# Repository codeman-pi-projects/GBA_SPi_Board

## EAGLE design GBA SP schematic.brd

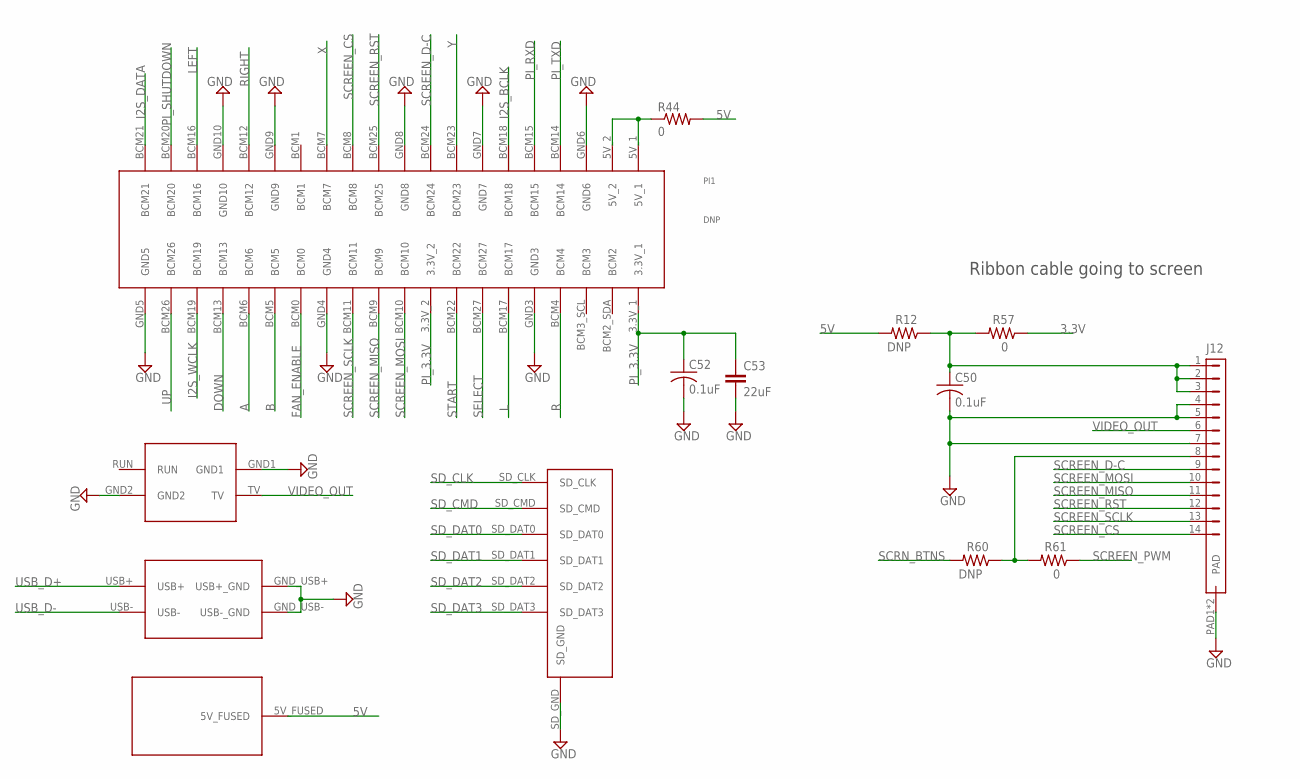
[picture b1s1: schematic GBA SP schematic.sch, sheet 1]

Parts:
C50, C52: 0.1uF; 0402_REAL; MPN CC0603ZRY5V9BB104; DIGIKEY 311-1343-1-ND
C53: 22uF; C0805; MPN LMK212BBJ226MG-T; DIGIKEY 587-5464-1-ND
J12: FPC_14; MPN 5051101492; DIGIKEY WM12370CT-ND
PI1: DNP; PI-ZERO
R12: DNP; R0603
R44: 0; R0805
R57: 0; R0603
R60: DNP; 0402_REAL
R61: 0; 0402_REAL

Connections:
3.3V: R57.1; also elsewhere on the board
5V: PI1.5V_FUSED, R12.2, R44.2; also elsewhere on the board
A: PI1.BCM6; also elsewhere on the board
B: PI1.BCM5; also elsewhere on the board
DOWN: PI1.BCM13; also elsewhere on the board
FAN_ENABLE: PI1.BCM0; also elsewhere on the board
GND: C50.2, C52.2, C53.2, J12.4, J12.5, J12.7, J12.PAD1 (PAD), J12.PAD2 (PAD), PI1.GND1, PI1.GND2, PI1.GND3, PI1.GND4, PI1.GND5, PI1.GND6, PI1.GND7, PI1.GND8, PI1.GND9, PI1.GND10, PI1.GND_USB+ (USB+_GND), PI1.GND_USB- (USB-_GND), PI1.SD_GND; also elsewhere on the board
I2S_BCLK: PI1.BCM18; also elsewhere on the board
I2S_DATA: PI1.BCM21; also elsewhere on the board
I2S_WCLK: PI1.BCM19; also elsewhere on the board
L: PI1.BCM17; also elsewhere on the board
LEFT: PI1.BCM16; also elsewhere on the board
unnamed: PI1.5V_1, PI1.5V_2, R44.1
unnamed: J12.8, R60.1, R61.2
unnamed: C50.1, J12.1, J12.2, J12.3, R12.1, R57.2
PI_3.3V: C52.1, C53.1, PI1.3.3V_1, PI1.3.3V_2; also elsewhere on the board
PI_RXD: PI1.BCM15; also elsewhere on the board
PI_SHUTDOWN: PI1.BCM20; also elsewhere on the board
PI_TXD: PI1.BCM14; also elsewhere on the board
R: PI1.BCM4; also elsewhere on the board
RIGHT: PI1.BCM12; also elsewhere on the board
SCREEN_CS: J12.14, PI1.BCM8
SCREEN_D-C: J12.9, PI1.BCM24
SCREEN_MISO: J12.11, PI1.BCM9
SCREEN_MOSI: J12.10, PI1.BCM10
SCREEN_PWM: R61.1; also elsewhere on the board
SCREEN_RST: J12.12, PI1.BCM25
SCREEN_SCLK: J12.13, PI1.BCM11
SCRN_BTNS: R60.2; also elsewhere on the board
SD_CLK: PI1.SD_CLK
SD_CMD: PI1.SD_CMD
SD_DAT0: PI1.SD_DAT0
SD_DAT1: PI1.SD_DAT1
SD_DAT2: PI1.SD_DAT2
SD_DAT3: PI1.SD_DAT3
SELECT: PI1.BCM27; also elsewhere on the board
START: PI1.BCM22; also elsewhere on the board
UP: PI1.BCM26; also elsewhere on the board
USB_D+: PI1.USB+; also elsewhere on the board
USB_D-: PI1.USB-; also elsewhere on the board
VIDEO_OUT: J12.6, PI1.TV
X: PI1.BCM7; also elsewhere on the board
Y: PI1.BCM23; also elsewhere on the board

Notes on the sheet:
Ribbon cable going to screen

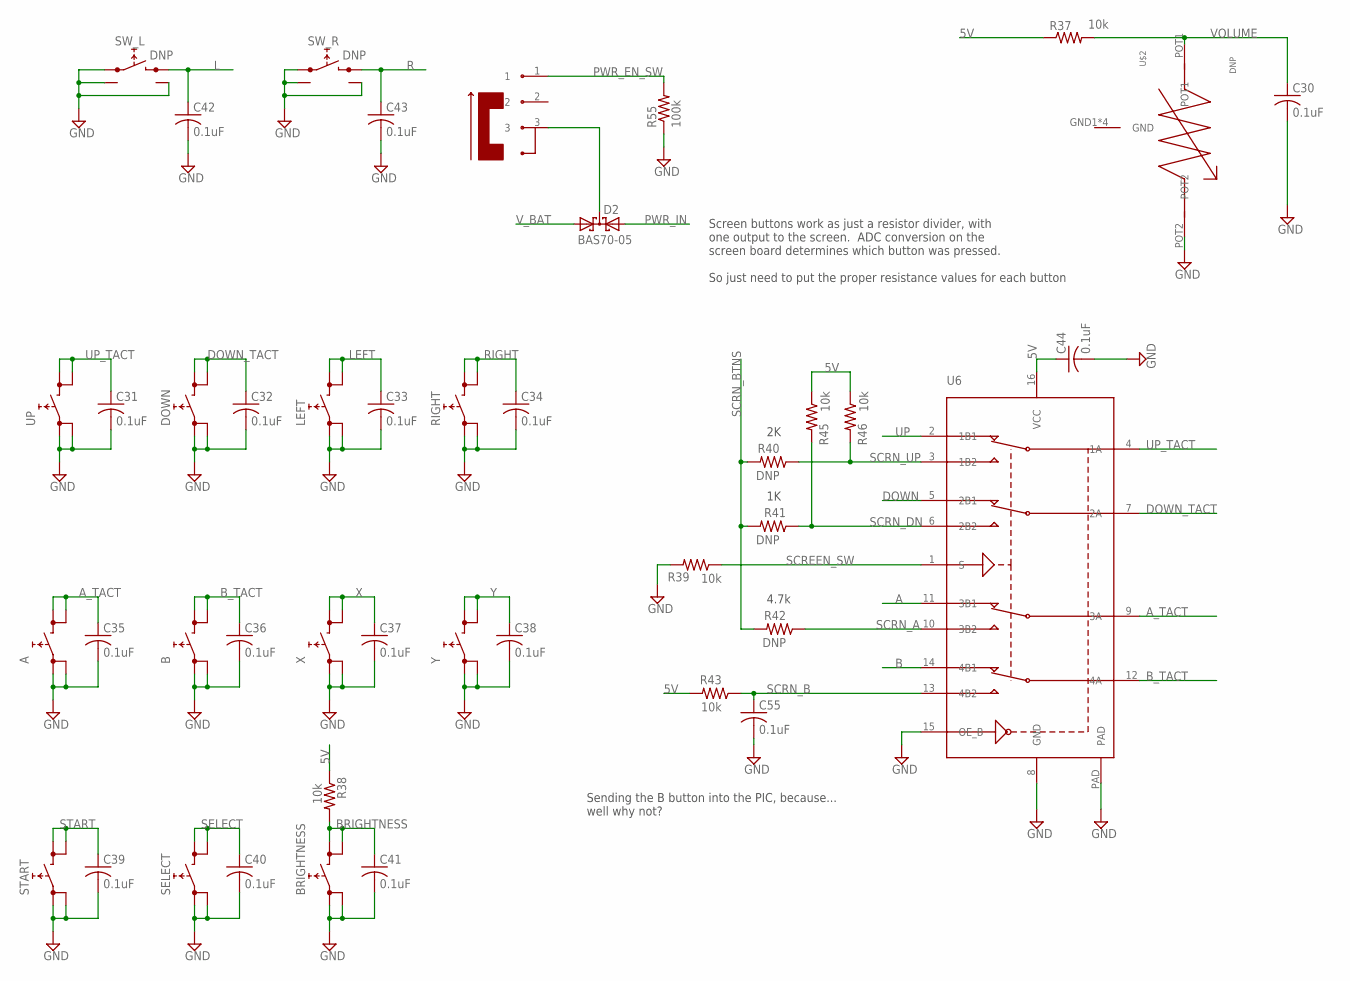
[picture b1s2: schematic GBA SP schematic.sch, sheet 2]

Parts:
A: TACTILEGBA_SP; GBA_SP_TACT; MPN SKRRAAE010; MOUSER 688-SKRRAA
B: TACTILEGBA_SP; GBA_SP_TACT; MPN SKRRAAE010; MOUSER 688-SKRRAA
BRIGHTNESS: TACTILE; TL3315; MPN TL3315NF160Q; DIGIKEY EG4621CT-ND
C30, C31, C32, C33, C34, C35, C36, C37, C38, C39, C40, C41, C42, C43, C44, C55: 0.1uF; 0402_REAL; MPN CC0603ZRY5V9BB104; DIGIKEY 311-1343-1-ND
D2: BAS70-05; SOT23; MPN BAS70-05-E3-08; DIGIKEY BAS70-05-E3-08CT-ND
DOWN: TACTILEGBA_SP; GBA_SP_TACT; MPN SKRRAAE010; MOUSER 688-SKRRAA
LEFT: TACTILEGBA_SP; GBA_SP_TACT; MPN SKRRAAE010; MOUSER 688-SKRRAA
R37, R38, R39, R43, R45, R46: 10k; 0402_REAL
R40: DNP; 0402_REAL; MPN ERJ-2RKF2001X; DIGIKEY P2.00KLCT-ND
R41, R42: DNP; 0402_REAL
R55: 100k; 0402_REAL; MPN RC0402FR-07100KL; DIGIKEY 311-100KLRCT-ND
RIGHT: TACTILEGBA_SP; GBA_SP_TACT; MPN SKRRAAE010; MOUSER 688-SKRRAA
SELECT: TACTILE; TL3315; MPN TL3315NF160Q; DIGIKEY EG4621CT-ND
START: TACTILE; TL3315; MPN TL3315NF160Q; DIGIKEY EG4621CT-ND
SW_L: DNP; GBA-SHOULDER-SW
SW_R: DNP; GBA-SHOULDER-SW
U6: SN74CBT3257C; VQFN16; MPN SN74CBT3257CRGYR; DIGIKEY 296-19212-1-ND
U$1: CSS-1210; MPN CSS-1210TB
U$2: DNP; GBA-POT
UP: TACTILEGBA_SP; GBA_SP_TACT; MPN SKRRAAE010; MOUSER 688-SKRRAA
X: TACTILEGBA_SP; GBA_SP_TACT; MPN SKRRAAE010; MOUSER 688-SKRRAA
Y: TACTILEGBA_SP; GBA_SP_TACT; MPN SKRRAAE010; MOUSER 688-SKRRAA

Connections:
5V: C44.1, R37.1, R38.1, R43.2, R45.1, R46.1, U6.16 (VCC); also elsewhere on the board
A: U6.11 (3B1); also elsewhere on the board
A_TACT: A.2 (3), A.4, C35.1, U6.9 (3A)
B: U6.14 (4B1); also elsewhere on the board
BRIGHTNESS: BRIGHTNESS.3, BRIGHTNESS.4, C41.1, R38.2; also elsewhere on the board
B_TACT: B.2 (3), B.4, C36.1, U6.12 (4A)
DOWN: U6.5 (2B1); also elsewhere on the board
DOWN_TACT: C32.1, DOWN.2 (3), DOWN.4, U6.7 (2A)
GND: A.1, A.3 (2), B.1, B.3 (2), BRIGHTNESS.1, BRIGHTNESS.2, C30.2, C31.2, C32.2, C33.2, C34.2, C35.2, C36.2, C37.2, C38.2, C39.2, C40.2, C41.2, C42.2, C43.2, C44.2, C55.2, DOWN.1, DOWN.3 (2), LEFT.1, LEFT.3 (2), R39.2, R55.1, RIGHT.1, RIGHT.3 (2), SELECT.1, SELECT.2, START.1, START.2, SW_L.A, SW_L.GND1, SW_L.GND2, SW_R.A, SW_R.GND1, SW_R.GND2, U6.8 (GND), U6.15 (OE_B), U6.PAD, U$2.POT2, UP.1, UP.3 (2), X.1, X.3 (2), Y.1, Y.3 (2); also elsewhere on the board
L: C42.1, SW_L.B; also elsewhere on the board
LEFT: C33.1, LEFT.2 (3), LEFT.4; also elsewhere on the board
unnamed: D2.3 (C), U$1.3
PWR_EN_SW: R55.2, U$1.1; also elsewhere on the board
PWR_IN: D2.2 (A2); also elsewhere on the board
R: C43.1, SW_R.B; also elsewhere on the board
RIGHT: C34.1, RIGHT.2 (3), RIGHT.4; also elsewhere on the board
SCREEN_SW: R39.1, U6.1 (S); also elsewhere on the board
SCRN_A: R42.1, U6.10 (3B2)
SCRN_B: C55.1, R43.1, U6.13 (4B2); also elsewhere on the board
SCRN_BTNS: R40.2, R41.2, R42.2; also elsewhere on the board
SCRN_DN: R41.1, R45.2, U6.6 (2B2); also elsewhere on the board
SCRN_UP: R40.1, R46.2, U6.3 (1B2); also elsewhere on the board
SELECT: C40.1, SELECT.3, SELECT.4; also elsewhere on the board
START: C39.1, START.3, START.4; also elsewhere on the board
UP: U6.2 (1B1); also elsewhere on the board
UP_TACT: C31.1, U6.4 (1A), UP.2 (3), UP.4
VOLUME: C30.1, R37.2, U$2.POT1; also elsewhere on the board
V_BAT: D2.1 (A1); also elsewhere on the board
X: C37.1, X.2 (3), X.4; also elsewhere on the board
Y: C38.1, Y.2 (3), Y.4; also elsewhere on the board

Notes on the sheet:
Screen buttons work as just a resistor divider, with one output to the screen. ADC conversion on the screen board determines which button was pressed. So just need to put the proper resistance values for each button
Sending the B button into the PIC, because... well why not?
4.7k

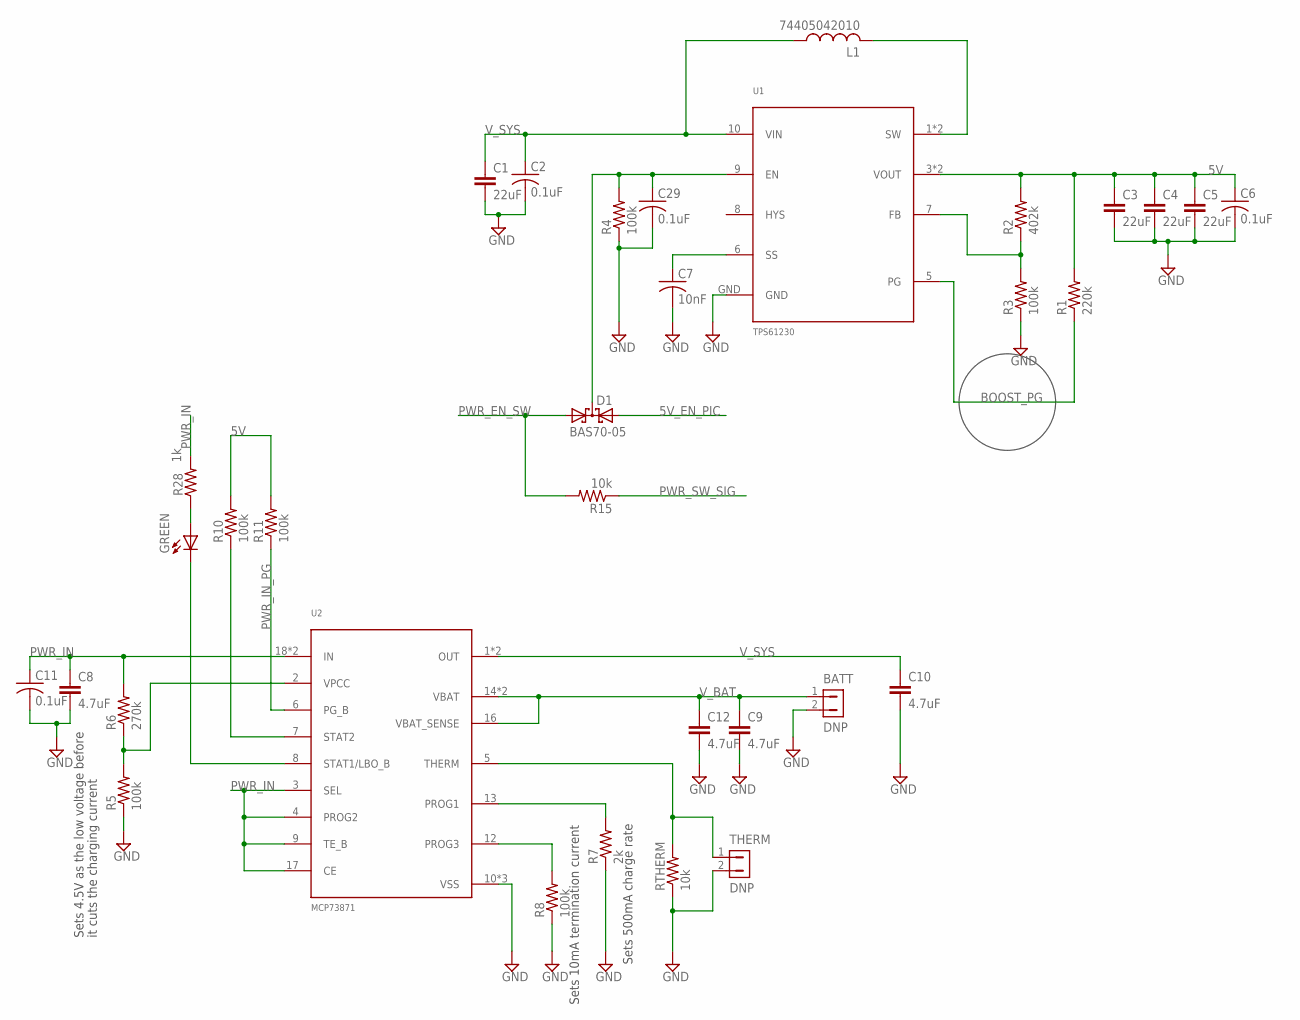
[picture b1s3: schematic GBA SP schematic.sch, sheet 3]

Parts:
BATT: DNP; HEADER-1X2
C1, C3, C4, C5: 22uF; C0805; MPN LMK212BBJ226MG-T; DIGIKEY 587-5464-1-ND
C2, C6, C11, C29: 0.1uF; 0402_REAL; MPN CC0603ZRY5V9BB104; DIGIKEY 311-1343-1-ND
C7: 10nF; 0402_REAL; MPN GRM155R71H103KA88D; DIGIKEY 490-4516-1-ND
C8, C9, C10, C12: 4.7uF; C0603; MPN CC0603KRX5R6BB475; DIGIKEY 311-1455-1-ND
D1: BAS70-05; SOT23; MPN BAS70-05-E3-08; DIGIKEY BAS70-05-E3-08CT-ND
GREEN: LEDCHIP-LED0603; CHIP-LED0603; MPN LTST-C191KGKT; DIGIKEY 160-1446-1-ND
L1: 74405042010; XFL4020-102MEB; MPN 74405042010
R1: 220k; R0603
R2: 402k; 0402_REAL; MPN RC0402FR-07402KL; DIGIKEY YAG3151CT-ND
R3, R4, R5, R8, R10, R11: 100k; 0402_REAL; MPN RC0402FR-07100KL; DIGIKEY 311-100KLRCT-ND
R6: 270k; R0603; MPN RC0402JR-07270KL; DIGIKEY 311-270KJRCT-ND
R7: 2k; 0402_REAL; MPN ERJ-2RKF2001X; DIGIKEY P2.00KLCT-ND
R15: 10k; 0402_REAL
R28: 1k; 0402_REAL
RTHERM: 10k; 0402_REAL
THERM: DNP; DF13-2_THIN
U1: TPS61230; VSON10; MPN TPS61230DRCR; DIGIKEY 296-37761-1-ND
U2: MCP73871; QFN20; MPN MCP73871-2AAI/ML; DIGIKEY MCP73871-2AAI/ML-ND

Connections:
5V: C3.1, C4.1, C5.1, C6.1, R1.2, R2.2, R10.2, R11.2, U1.3 (VOUT), U1.4 (VOUT); also elsewhere on the board
5V_EN_PIC: D1.2 (A2); also elsewhere on the board
BOOST_PG: R1.1, U1.5 (PG)
GND: BATT.2, C1.2, C2.2, C3.2, C4.2, C5.2, C6.2, C7.2, C8.2, C9.2, C10.2, C11.2, C12.2, C29.2, R3.1, R4.1, R5.1, R7.1, R8.1, RTHERM.1, THERM.2, U1.GND, U2.10 (VSS), U2.11 (VSS), U2.PAD (VSS); also elsewhere on the board
unnamed: C29.1, D1.3 (C), R4.2, U1.9 (EN)
unnamed: L1.2, U1.1 (SW), U1.2 (SW)
unnamed: R2.1, R3.2, U1.7 (FB)
unnamed: R7.2, U2.13 (PROG1)
unnamed: R5.2, R6.1, U2.2 (VPCC)
unnamed: C7.1, U1.6 (SS)
unnamed: R8.2, U2.12 (PROG3)
unnamed: RTHERM.2, THERM.1, U2.5 (THERM)
unnamed: GREEN.A, R28.1
PWR_EN_SW: D1.1 (A1), R15.2; also elsewhere on the board
PWR_IN: C8.1, C11.1, R6.2, R28.2, U2.3 (SEL), U2.4 (PROG2), U2.9 (TE_B), U2.17 (CE), U2.18 (IN), U2.19 (IN); also elsewhere on the board
PWR_IN_PG: R11.1, U2.6 (PG_B); also elsewhere on the board
PWR_SW_SIG: R15.1; also elsewhere on the board
STAT1: GREEN.C, U2.8 (STAT1/LBO_B)
STAT2: R10.1, U2.7 (STAT2)
V_BAT: BATT.1, C9.1, C12.1, U2.14 (VBAT), U2.15 (VBAT), U2.16 (VBAT_SENSE); also elsewhere on the board
V_SYS: C1.1, C2.1, C10.1, L1.1, U1.10 (VIN), U2.1 (OUT), U2.20 (OUT)

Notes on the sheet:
Sets 4.5V as the low voltage before
it cuts the charging current
Sets 500mA charge rate
Sets 10mA termination current

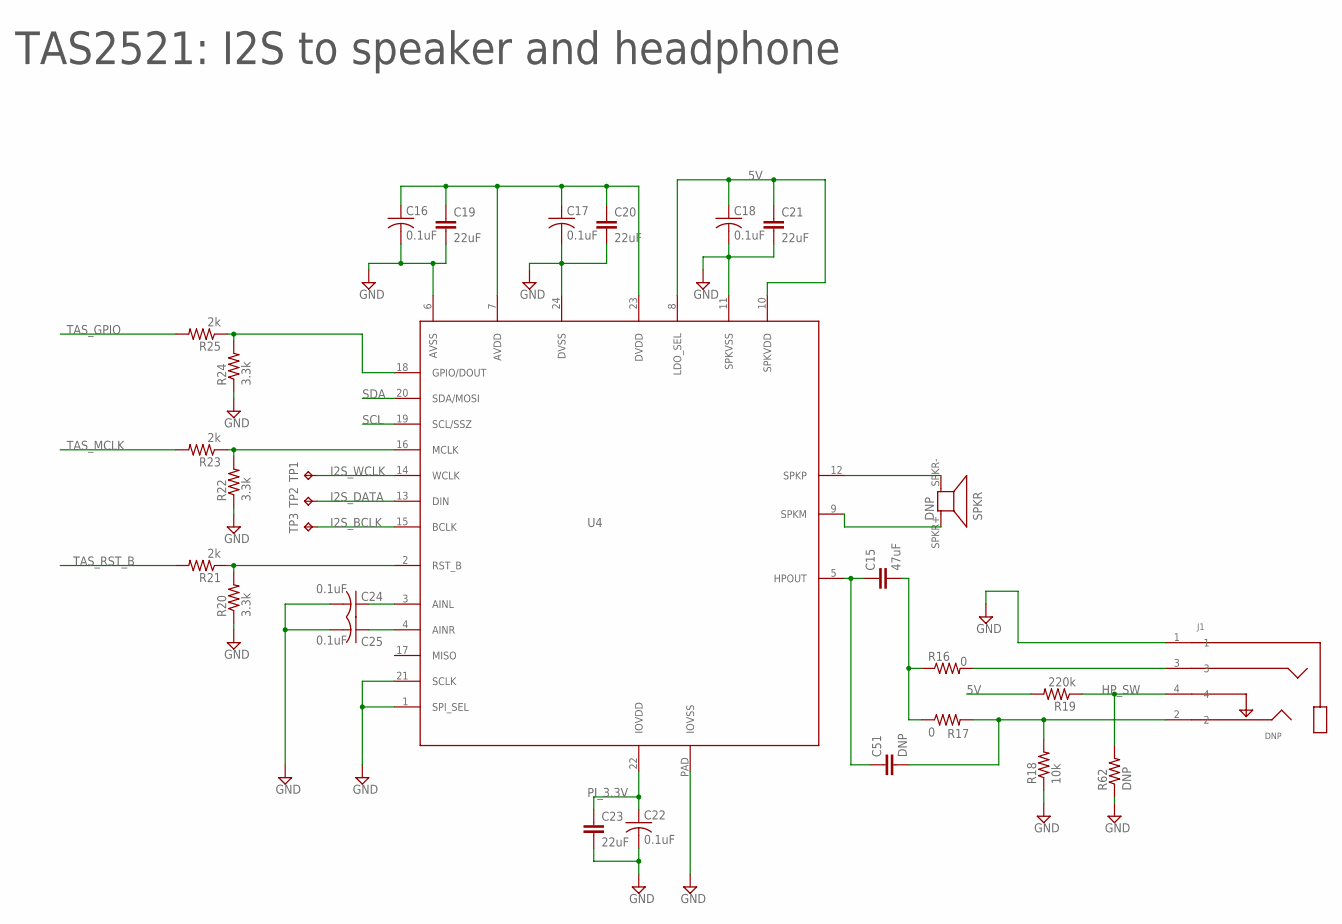
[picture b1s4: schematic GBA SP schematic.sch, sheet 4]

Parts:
C15: 47uF; C0805; MPN GRM21BR61A476ME15L; DIGIKEY 490-9961-1-ND
C16, C17, C18, C22, C24, C25: 0.1uF; 0402_REAL; MPN CC0603ZRY5V9BB104; DIGIKEY 311-1343-1-ND
C19, C20, C21, C23: 22uF; C0805; MPN LMK212BBJ226MG-T; DIGIKEY 587-5464-1-ND
C51: DNP; C0805; MPN GRM21BR61A476ME15L; DIGIKEY 490-9961-1-ND
J1: DNP; HEADPHONE_JACK; MPN SJ-3524-SMT; DIGIKEY CP-3524SJCT-ND
R16, R17: 0; 0402_REAL
R18: 10k; 0402_REAL
R19: 220k; R0603
R20, R22, R24: 3.3k; 0402_REAL
R21, R23, R25: 2k; 0402_REAL; MPN ERJ-2RKF2001X; DIGIKEY P2.00KLCT-ND
R62: DNP; 0402_REAL
SPKR: DNP; GBA-SPKR
TP1, TP2, TP3: TPTP06R; TP06R
U4: TAS2521; QFN24; MPN TAS2521IRGET; DIGIKEY 296-35781-1-ND

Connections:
5V: C18.1, C21.1, R19.2, U4.8 (LDO_SEL), U4.10 (SPKVDD); also elsewhere on the board
GND: C16.2, C17.2, C18.2, C19.2, C20.2, C21.2, C22.2, C23.2, C24.2, C25.2, J1.1, R18.1, R20.1, R22.1, R24.1, R62.1, U4.1 (SPI_SEL), U4.6 (AVSS), U4.11 (SPKVSS), U4.21 (SCLK), U4.24 (DVSS), U4.PAD (IOVSS); also elsewhere on the board
HP_SW: J1.4, R19.1, R62.2; also elsewhere on the board
I2S_BCLK: TP3.TP, U4.15 (BCLK); also elsewhere on the board
I2S_DATA: TP2.TP, U4.13 (DIN); also elsewhere on the board
I2S_WCLK: TP1.TP, U4.14 (WCLK); also elsewhere on the board
unnamed: SPKR.SPKR- (-), U4.12 (SPKP)
unnamed: SPKR.SPKR+ (+), U4.9 (SPKM)
unnamed: C15.1, C51.1, U4.5 (HPOUT)
unnamed: C15.2, R16.1, R17.1
unnamed: J1.3, R16.2
unnamed: C51.2, J1.2, R17.2, R18.2
unnamed: C16.1, C17.1, C19.1, C20.1, U4.7 (AVDD), U4.23 (DVDD)
unnamed: R20.2, R21.1, U4.2 (RST_B)
unnamed: R22.2, R23.1, U4.16 (MCLK)
unnamed: R24.2, R25.1, U4.18 (GPIO/DOUT)
unnamed: C24.1, U4.3 (AINL)
unnamed: C25.1, U4.4 (AINR)
PI_3.3V: C22.1, C23.1, U4.22 (IOVDD); also elsewhere on the board
SCL: U4.19 (SCL/SSZ); also elsewhere on the board
SDA: U4.20 (SDA/MOSI); also elsewhere on the board
TAS_GPIO: R25.2
TAS_MCLK: R23.2
TAS_RST_B: R21.2; also elsewhere on the board

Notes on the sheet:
TAS2521: I2S to speaker and headphone

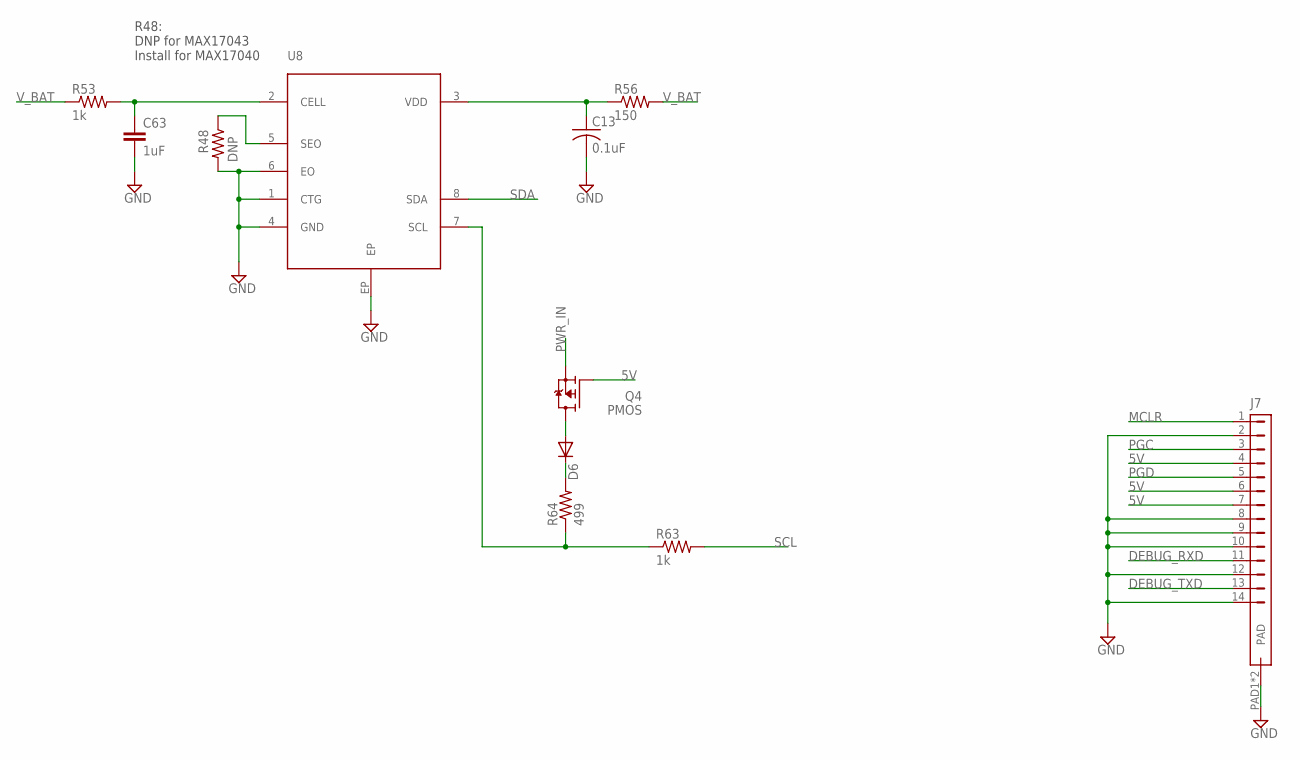
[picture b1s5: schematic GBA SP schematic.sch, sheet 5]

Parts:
C13: 0.1uF; 0402_REAL; MPN CC0603ZRY5V9BB104; DIGIKEY 311-1343-1-ND
C63: 1uF; 0402_REAL
D6: DIODE-SOD523; SOD523
J7: FPC_14; MPN 5051101492; DIGIKEY WM12370CT-ND
Q4: PMOS; SC70
R48: DNP; 0402_REAL
R53, R63: 1k; 0402_REAL
R56: 150; 0402_REAL
R64: 499; 0402_REAL
U8: MAX17040; TDFN-2X3; MPN MAX17043

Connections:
5V: J7.4, J7.6, J7.7, Q4.G; also elsewhere on the board
DEBUG_RXD: J7.11; also elsewhere on the board
DEBUG_TXD: J7.13; also elsewhere on the board
GND: C13.2, C63.2, J7.2, J7.8, J7.9, J7.10, J7.12, J7.14, J7.PAD1 (PAD), J7.PAD2 (PAD), R48.2, U8.1 (CTG), U8.4 (GND), U8.6 (EO), U8.EP; also elsewhere on the board
MCLR: J7.1; also elsewhere on the board
unnamed: R48.1, U8.5 (SEO)
unnamed: D6.C, R64.2
unnamed: D6.A, Q4.D
unnamed: C63.1, R53.2, U8.2 (CELL)
unnamed: C13.1, R56.1, U8.3 (VDD)
unnamed: R63.1, R64.1, U8.7 (SCL)
PGC: J7.3; also elsewhere on the board
PGD: J7.5; also elsewhere on the board
PWR_IN: Q4.S; also elsewhere on the board
SCL: R63.2; also elsewhere on the board
SDA: U8.8 (SDA); also elsewhere on the board
V_BAT: R53.1, R56.2; also elsewhere on the board

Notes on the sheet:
R48: DNP for MAX17043 Install for MAX17040

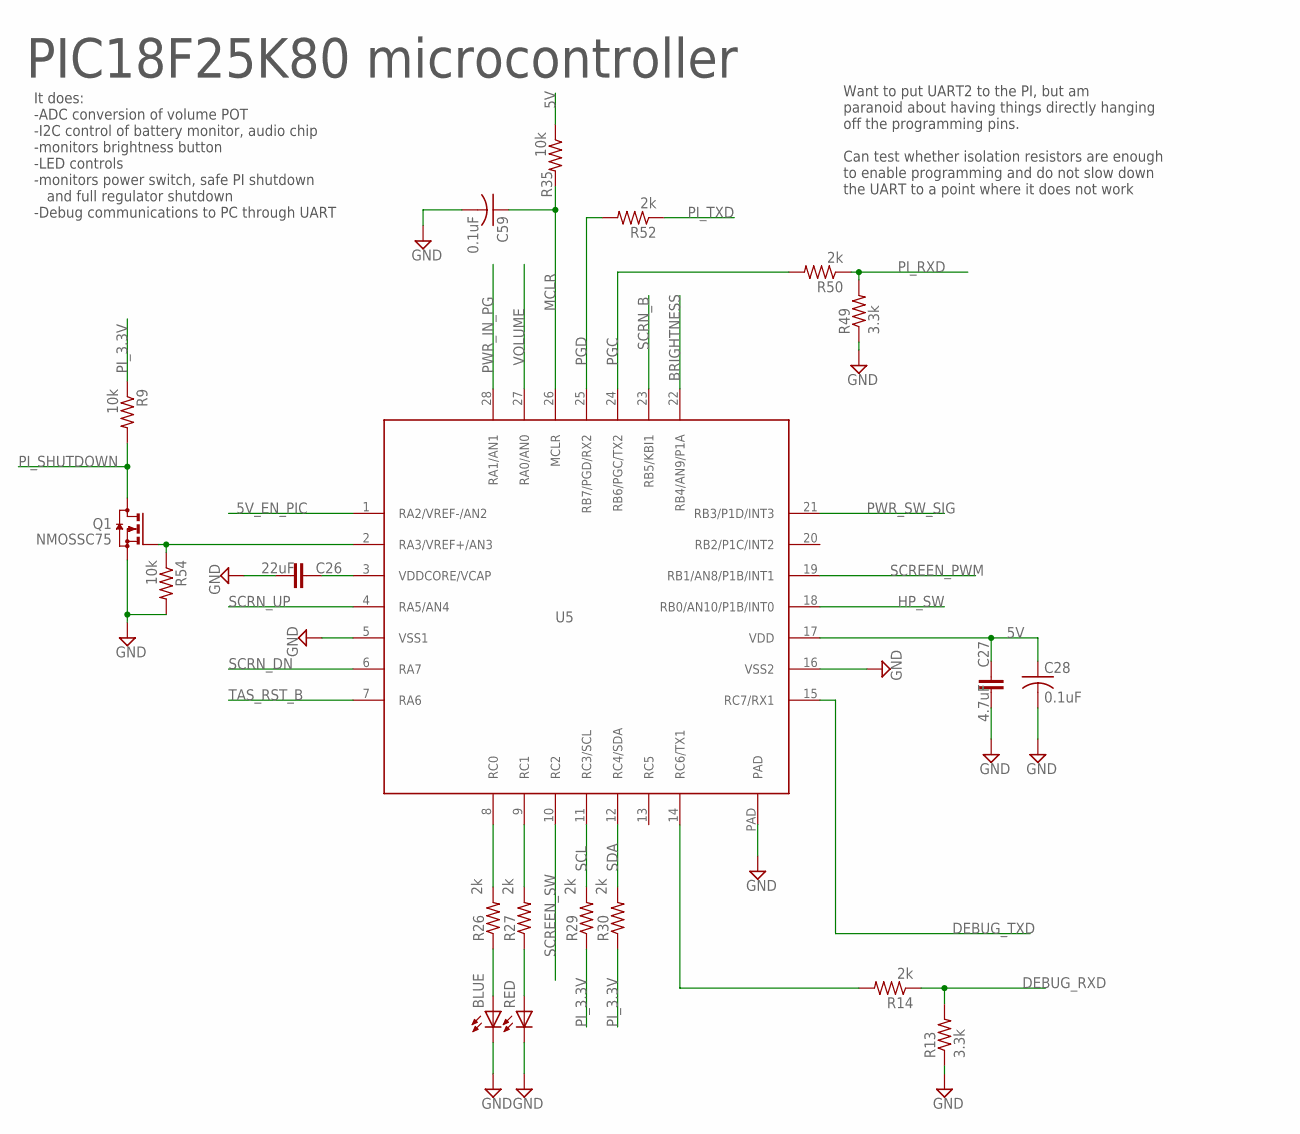
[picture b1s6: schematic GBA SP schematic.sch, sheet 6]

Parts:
BLUE: LEDCHIP-LED0603; CHIP-LED0603; MPN LTST-C193TBKT-5A; DIGIKEY 160-1827-1-ND
C26: 22uF; C0805; MPN LMK212BBJ226MG-T; DIGIKEY 587-5464-1-ND
C27: 4.7uF; C0603; MPN CC0603KRX5R6BB475; DIGIKEY 311-1455-1-ND
C28, C59: 0.1uF; 0402_REAL; MPN CC0603ZRY5V9BB104; DIGIKEY 311-1343-1-ND
Q1: NMOSSC75; SC75; MPN NTA4001NT1G; DIGIKEY NTA4001NT1GOSCT-ND
R9, R35, R54: 10k; 0402_REAL
R13, R49: 3.3k; 0402_REAL
R14, R26, R27, R29, R30, R50, R52: 2k; 0402_REAL; MPN ERJ-2RKF2001X; DIGIKEY P2.00KLCT-ND
RED: LEDCHIP-LED0603; CHIP-LED0603; MPN LTST-C191KRKT; DIGIKEY 160-1447-1-ND
U5: PIC18F25K80; QFN-S_28; MPN PIC18F25K80-I/MM; DIGIKEY PIC18F25K80-I/MM-ND

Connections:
5V: C27.1, C28.1, R35.1, U5.17 (VDD); also elsewhere on the board
5V_EN_PIC: U5.1 (RA2/VREF-/AN2); also elsewhere on the board
BRIGHTNESS: U5.22 (RB4/AN9/P1A); also elsewhere on the board
DEBUG_RXD: R13.2, R14.1; also elsewhere on the board
DEBUG_TXD: U5.15 (RC7/RX1); also elsewhere on the board
GND: BLUE.C, C26.2, C27.2, C28.2, C59.2, Q1.S, R13.1, R49.1, R54.2, RED.C, U5.5 (VSS1), U5.16 (VSS2), U5.PAD; also elsewhere on the board
HP_SW: U5.18 (RB0/AN10/P1B/INT0); also elsewhere on the board
MCLR: C59.1, R35.2, U5.26 (MCLR); also elsewhere on the board
unnamed: R14.2, U5.14 (RC6/TX1)
unnamed: Q1.G, R54.1, U5.2 (RA3/VREF+/AN3)
unnamed: R27.1, RED.A
unnamed: BLUE.A, R26.1
unnamed: R27.2, U5.9 (RC1)
unnamed: R26.2, U5.8 (RC0)
unnamed: C26.1, U5.3 (VDDCORE/VCAP)
PGC: R50.2, U5.24 (RB6/PGC/TX2); also elsewhere on the board
PGD: R52.2, U5.25 (RB7/PGD/RX2); also elsewhere on the board
PI_3.3V: R9.1, R29.1, R30.1; also elsewhere on the board
PI_RXD: R49.2, R50.1; also elsewhere on the board
PI_SHUTDOWN: Q1.D, R9.2; also elsewhere on the board
PI_TXD: R52.1; also elsewhere on the board
PWR_IN_PG: U5.28 (RA1/AN1); also elsewhere on the board
PWR_SW_SIG: U5.21 (RB3/P1D/INT3); also elsewhere on the board
SCL: R29.2, U5.11 (RC3/SCL); also elsewhere on the board
SCREEN_PWM: U5.19 (RB1/AN8/P1B/INT1); also elsewhere on the board
SCREEN_SW: U5.10 (RC2); also elsewhere on the board
SCRN_B: U5.23 (RB5/KBI1); also elsewhere on the board
SCRN_DN: U5.6 (RA7); also elsewhere on the board
SCRN_UP: U5.4 (RA5/AN4); also elsewhere on the board
SDA: R30.2, U5.12 (RC4/SDA); also elsewhere on the board
TAS_RST_B: U5.7 (RA6); also elsewhere on the board
VOLUME: U5.27 (RA0/AN0); also elsewhere on the board

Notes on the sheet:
PIC18F25K80 microcontroller
It does: -ADC conversion of volume POT -I2C control of battery monitor, audio chip -monitors brightness button -LED controls -monitors power switch, safe PI shutdown and full regulator shutdown -Debug communications to PC through UART
Want to put UART2 to the PI, but am paranoid about having things directly hanging off the programming pins. Can test whether isolation resistors are enough to enable programming and do not slow down the UART to a point where it does not work

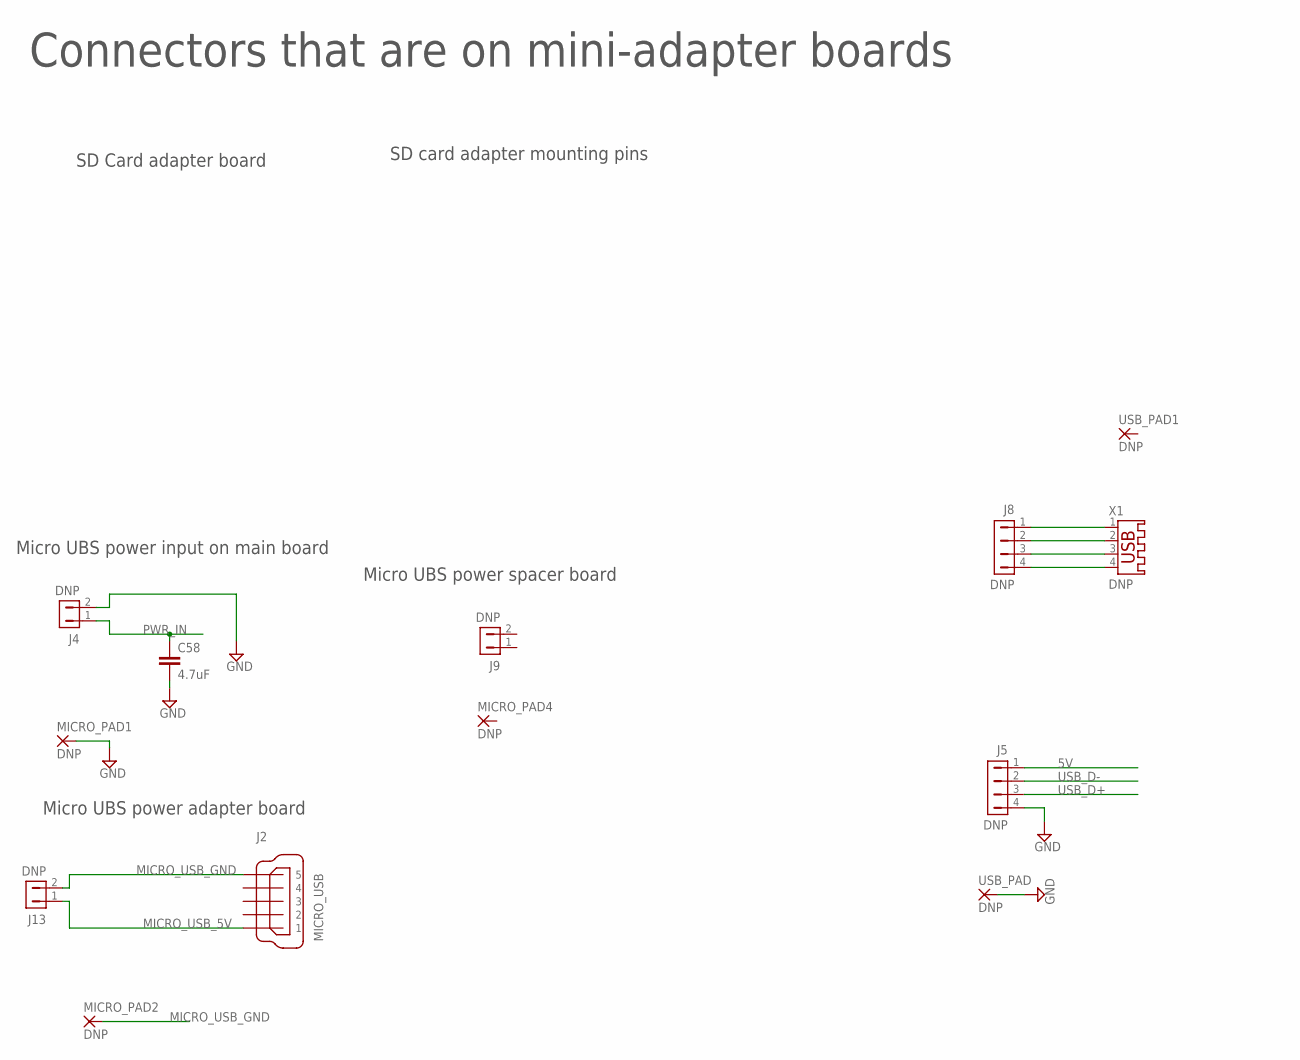
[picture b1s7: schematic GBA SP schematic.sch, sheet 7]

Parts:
C58: 4.7uF; C0603; MPN CC0603KRX5R6BB475; DIGIKEY 311-1455-1-ND
J2: MICRO_USB; MPN 10118192-0001LF; DIGIKEY 609-4613-1-ND
J4, J9, J13: DNP; USB_PWR_2PIN
J5, J8: DNP; USB_4PIN
MICRO_PAD1, MICRO_PAD2, MICRO_PAD4: DNP; 1,6/0,8
USB_PAD, USB_PAD1: DNP; 1,6/0,8
X1: DNP; USB-A003; MPN 87583-2010BLF; DIGIKEY 609-4413-ND

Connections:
5V: J5.1; also elsewhere on the board
GND: C58.2, J4.2, J5.4, MICRO_PAD1.1, USB_PAD.1; also elsewhere on the board
MICRO_USB_5V: J2.1, J13.1
MICRO_USB_GND: J2.5, J13.2, MICRO_PAD2.1
unnamed: J8.1, X1.1
unnamed: J8.2, X1.2
unnamed: J8.3, X1.3
unnamed: J8.4, X1.4
PWR_IN: C58.1, J4.1; also elsewhere on the board
USB_D+: J5.3; also elsewhere on the board
USB_D-: J5.2; also elsewhere on the board

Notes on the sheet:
Connectors that are on mini-adapter boards
SD Card adapter board
SD card adapter mounting pins
Micro UBS power input on main board
Micro UBS power adapter board
Micro UBS power spacer board

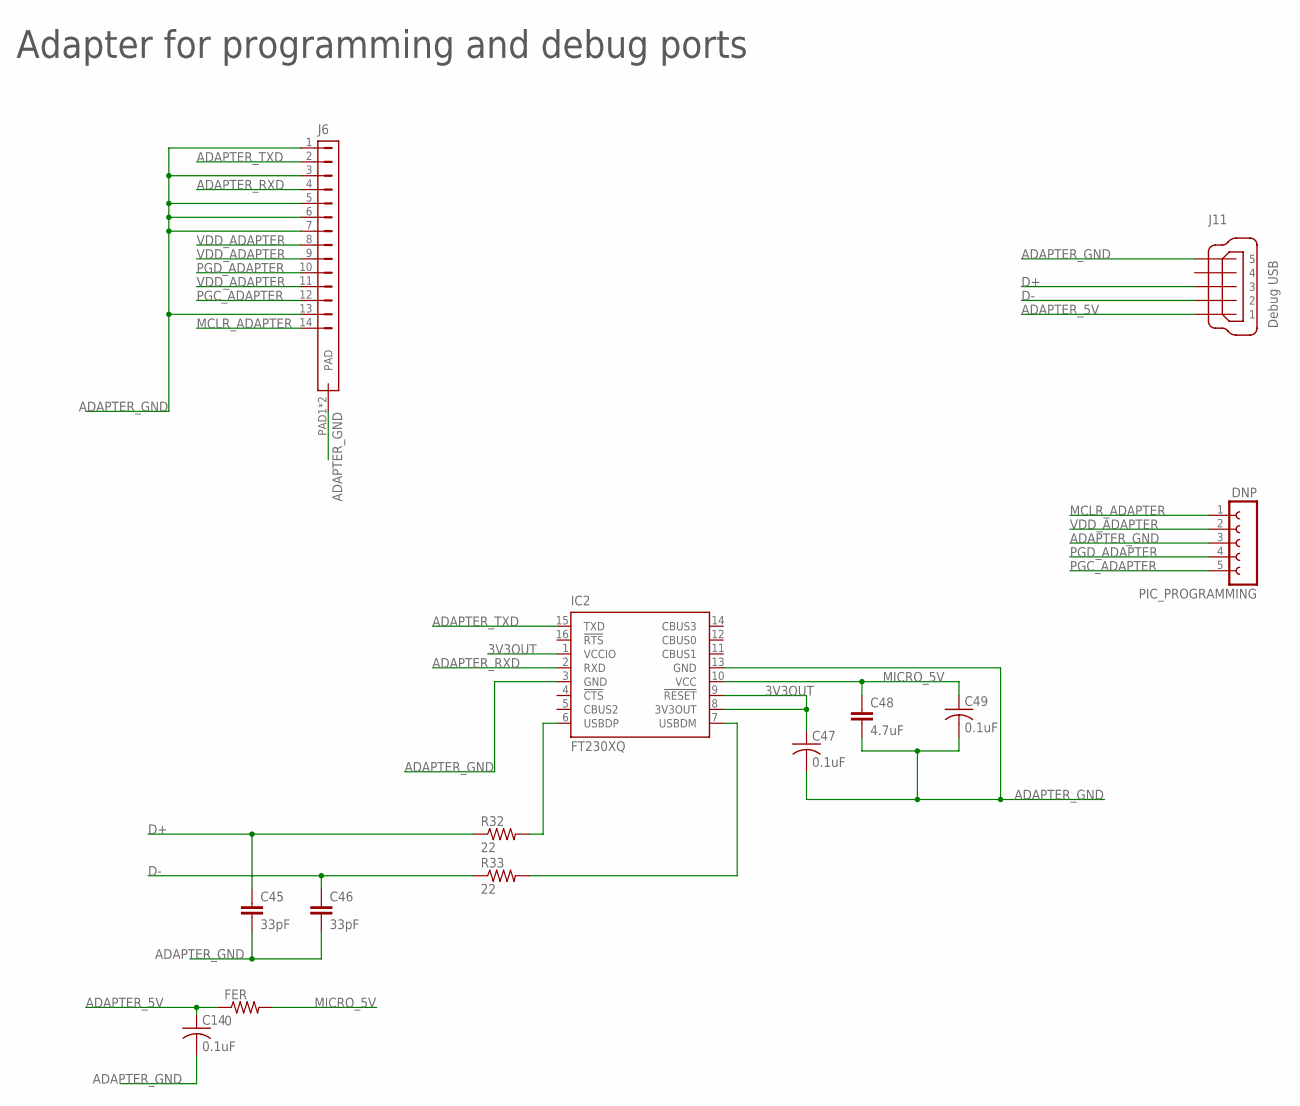
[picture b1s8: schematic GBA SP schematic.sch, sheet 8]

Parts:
C14, C47, C49: 0.1uF; 0402_REAL; MPN CC0603ZRY5V9BB104; DIGIKEY 311-1343-1-ND
C45, C46: 33pF; 0402_REAL
C48: 4.7uF; C0603; MPN CC0603KRX5R6BB475; DIGIKEY 311-1455-1-ND
FER: 0; R0603
IC2: FT230XQ; QFN16; MPN FT230XQ-R; DIGIKEY 768-1130-1-ND
J6: FPC_14; MPN 5051101492; DIGIKEY WM12370CT-ND
J11: Debug USB; MICRO_USB; MPN 10118192-0001LF; DIGIKEY 609-4613-1-ND
PIC_PROGRAMMING: DNP; FE05-1; MPN PPTC051LGBN-RC; DIGIKEY S5441-ND
R32, R33: 22; 0402_REAL

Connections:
3V3OUT: C47.1, IC2.1 (VCCIO), IC2.8 (3V3OUT), IC2.9 (!RESET)
ADAPTER_5V: C14.1, FER.1, J11.1
ADAPTER_GND: C14.2, C45.2, C46.2, C47.2, C48.2, C49.2, IC2.3 (GND), IC2.13 (GND), J6.1, J6.3, J6.5, J6.6, J6.7, J6.13, J6.PAD1 (PAD), J6.PAD2 (PAD), J11.5, PIC_PROGRAMMING.3
ADAPTER_RXD: IC2.2 (RXD), J6.4
ADAPTER_TXD: IC2.15 (TXD), J6.2
D+: C45.1, J11.3, R32.1
D-: C46.1, J11.2, R33.1
DM: IC2.7 (USBDM), R33.2
DP: IC2.6 (USBDP), R32.2
MCLR_ADAPTER: J6.14, PIC_PROGRAMMING.1
MICRO_5V: C48.1, C49.1, FER.2, IC2.10 (VCC)
PGC_ADAPTER: J6.12, PIC_PROGRAMMING.5
PGD_ADAPTER: J6.10, PIC_PROGRAMMING.4
VDD_ADAPTER: J6.8, J6.9, J6.11, PIC_PROGRAMMING.2

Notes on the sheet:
Adapter for programming and debug ports

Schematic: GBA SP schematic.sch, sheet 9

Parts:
C60: 0.1uF; 0402_REAL; MPN CC0603ZRY5V9BB104; DIGIKEY 311-1343-1-ND
J14: FPC_14; MPN 5051101492; DIGIKEY WM12370CT-ND
Q2: NMOSSC75; SC75; MPN NTA4001NT1G; DIGIKEY NTA4001NT1GOSCT-ND
R47: 22; 0402_REAL
SCREEN1: DNP; SPI_SCREEN
SV1: DNP; FE06-2

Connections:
BTNS-PWM: J14.7, Q2.G, SV1.8
K: R47.1, SCREEN1.11, SCREEN1.12, SCREEN1.13, SCREEN1.14
unnamed: Q2.D, R47.2
SCREEN_PWR: C60.1, J14.12, J14.13, J14.14, SCREEN1.9, SCREEN1.10, SV1.11
SPI_CS: J14.1, SCREEN1.5, SV1.3
SPI_D-C: J14.6, SCREEN1.4, SV1.7
SPI_MISO: J14.4, SCREEN1.7, SV1.5
SPI_MOSI: J14.5, SCREEN1.6, SV1.6
SPI_RST: J14.3, SCREEN1.2, SV1.2
SPI_SCLK: J14.2, SCREEN1.3, SV1.4
VIDEO_GND: C60.2, J14.8, J14.10, J14.11, J14.PAD1 (PAD), J14.PAD2 (PAD), Q2.S, SCREEN1.1, SCREEN1.8, SV1.1, SV1.9, SV1.12
VIDEO_SIG: J14.9, SV1.10
XL: SCREEN1.15
XR: SCREEN1.17
YD: SCREEN1.18
YU: SCREEN1.16

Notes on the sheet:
Ribbon cable from main board going to screen
LED ANODE

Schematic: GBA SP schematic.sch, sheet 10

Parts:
C54: 22uF; C0805; MPN LMK212BBJ226MG-T; DIGIKEY 587-5464-1-ND
C61: 6.8pF; 0402_REAL; MPN CC0402DRNPO9BN6R8; DIGIKEY 311-1637-1-ND
C62: 4.7uF; C0603; MPN CC0603KRX5R6BB475; DIGIKEY 311-1455-1-ND
FAN: DNP; HEADER-1X2
L2: 2.2uH; L2520; MPN LQM2HPN2R2MG0L; DIGIKEY 490-5114-2-ND
Q3: DNP; TSOT23-6; MPN FDC637BNZ; DIGIKEY FDC637BNZCT-ND
R31: 100k; 0402_REAL; MPN RC0402FR-07100KL; DIGIKEY 311-100KLRCT-ND
R34: 442k; 0402_REAL; MPN RC0402FR-07442KL; DIGIKEY 311-442KLRCT-ND
R36, R51: 10k; 0402_REAL
R58: 0; 0402_REAL
R59: DNP; 0402_REAL
U7: TLV62568; SOT-563; MPN TLV62568DRLT; DIGIKEY 296-46649-1-ND

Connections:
3.3V: C54.1, C61.1, L2.2, R34.2; also elsewhere on the board
3.3V_EN: R36.1, U7.5 (EN)
5V: C62.1, FAN.1, R58.1, U7.3 (VIN); also elsewhere on the board
FAN_ENABLE: Q3.3 (G), R51.1; also elsewhere on the board
GND: C54.2, C62.2, Q3.4 (S), R31.1, R51.2, R59.2, U7.2 (GND); also elsewhere on the board
unnamed: R36.2, R58.2, R59.1
unnamed: L2.1, U7.4 (SW)
unnamed: C61.2, R31.2, R34.1, U7.1 (FB)
unnamed: FAN.2, Q3.1 (D), Q3.2 (D), Q3.5 (D), Q3.6 (D)
